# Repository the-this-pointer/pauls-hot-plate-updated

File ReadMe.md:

#### Paul's Hotplate Upgraded

This is another version of awesome pauls hot plate project that I am working on. I designed a pcb for the project because I don't have access to the board he used in his project.
The project is not completed yet and I should do some modifications on the enclosure, and I need to change the firmware to support the new PCB. Also the enclosure and the PCB is not tested.

External component libraries located [here](https://github.com/the-this-pointer/kicad-my-libraries)

###### TODO:

- Firmware for new PCB
- Enclosure for new PCB

#### Images

The enclosure files and images are for revision `54e05cd389d`, the boards are changed afterwards and I will redesign enclosure.

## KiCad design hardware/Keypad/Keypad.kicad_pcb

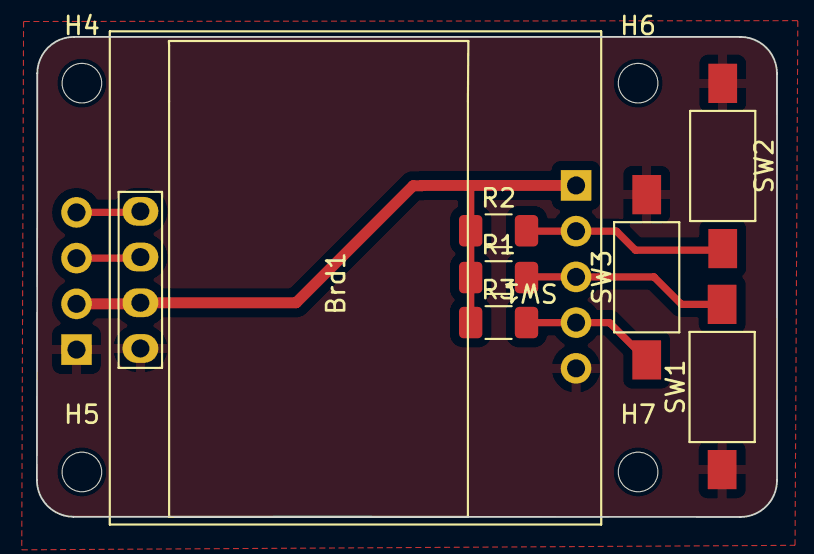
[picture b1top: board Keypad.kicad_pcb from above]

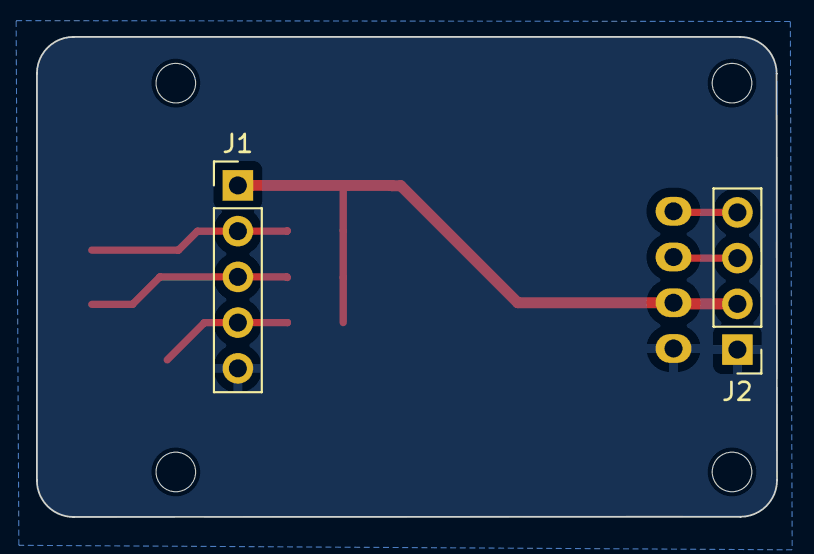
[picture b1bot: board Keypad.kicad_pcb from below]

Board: 2 copper layers, 41.1 x 26.7 mm, 13 parts (2 on the bottom side), 7 nets.

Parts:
Brd1: SSD1306; 128x64OLED
H4, H5, H6, H7: MountingHole; MountingHole_2.2mm_M2
J1: Keypad1; PinHeader_1x05_P2.54mm_Vertical
J2: LCD; PinHeader_1x04_P2.54mm_Vertical
R1, R2, R3: 10k; R_1206_3216Metric_Pad1.30x1.75mm_HandSolder
SW1: LEFT; SW_SPST_FSMSM
SW2: RIGHT; SW_SPST_FSMSM
SW3: SET; SW_SPST_FSMSM

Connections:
+3V3: Brd1.2 (VCC), J1.1, J2.2, R1.1, R2.1, R3.1
/IO12: J1.4, R3.2, SW3.2 (B)
/IO13: J1.2, R2.2, SW2.2 (B)
/IO14: J1.3, R1.2, SW1.2 (B)
/SCK: Brd1.3 (SCL), J2.3
/SDA: Brd1.4 (SDA), J2.4
GND: Brd1.1 (GND), J1.5, J2.1, SW1.1 (A), SW2.1 (A), SW3.1 (A)

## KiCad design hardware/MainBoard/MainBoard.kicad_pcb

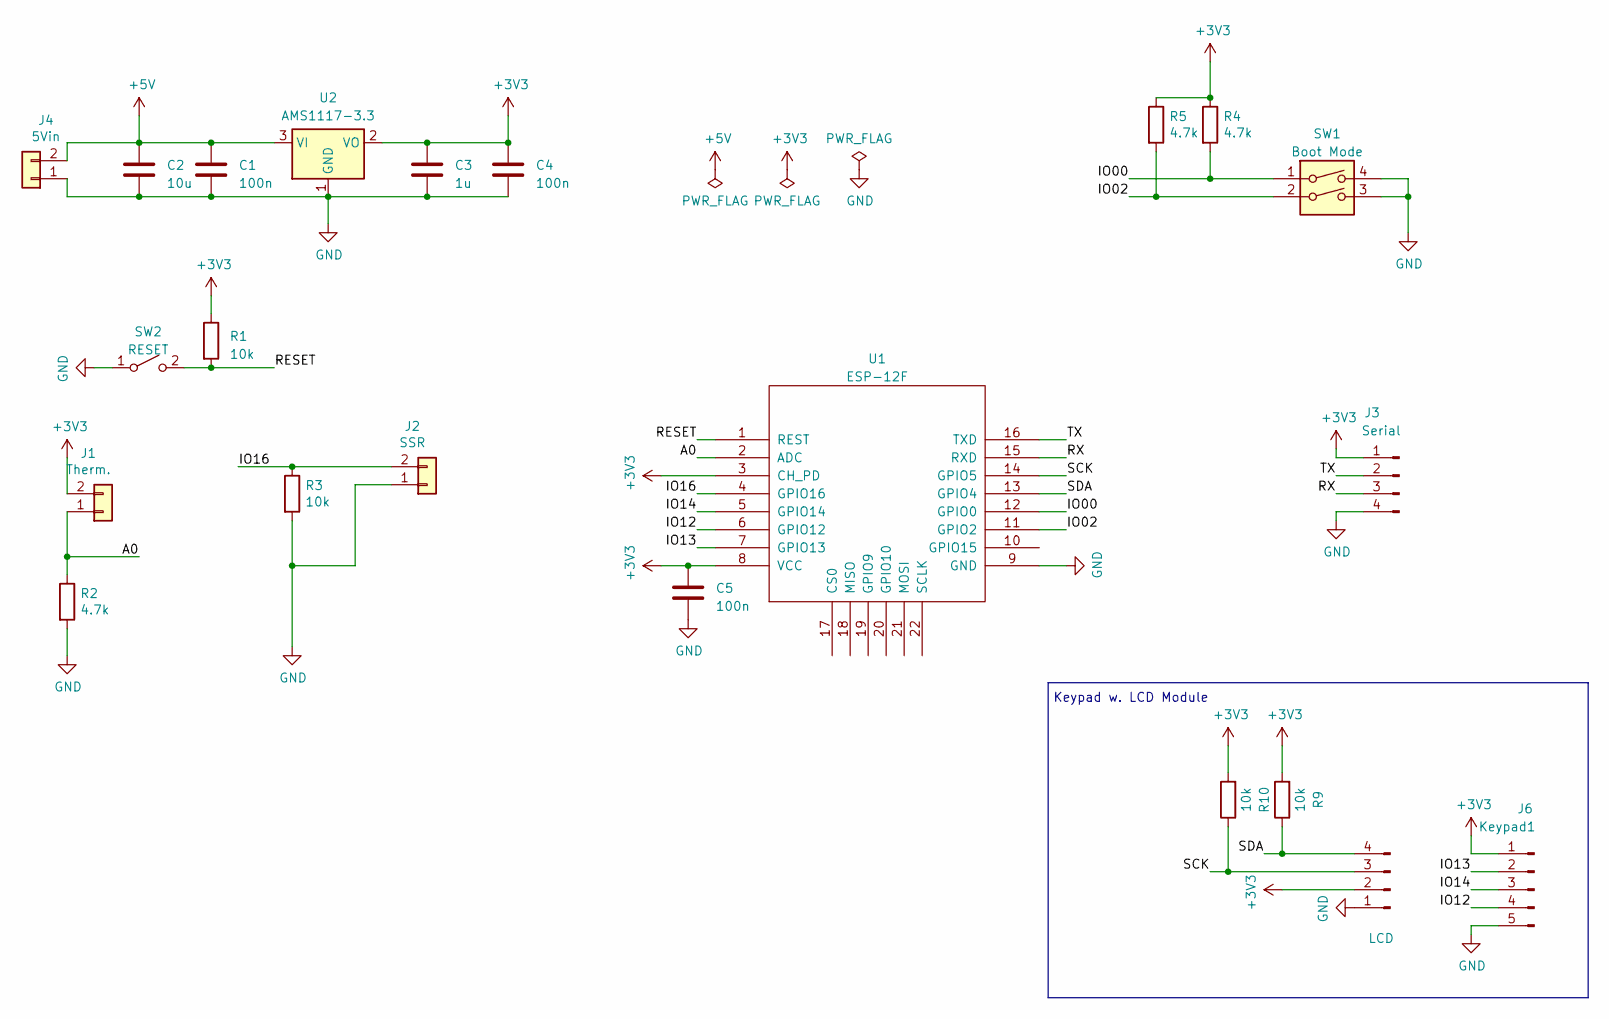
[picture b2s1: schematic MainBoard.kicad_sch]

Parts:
C1, C4, C5: 100n; C_1206_3216Metric_Pad1.33x1.80mm_HandSolder
C2: 10u; C_1206_3216Metric_Pad1.33x1.80mm_HandSolder
C3: 1u; C_1206_3216Metric_Pad1.33x1.80mm_HandSolder
J1: Therm.; JST_XH_B2B-XH-A_1x02_P2.50mm_Vertical
J2: SSR; JST_XH_B2B-XH-A_1x02_P2.50mm_Vertical
J3: Serial; PinHeader_1x04_P2.54mm_Vertical
J4: 5Vin; JST_XH_B2B-XH-A_1x02_P2.50mm_Vertical
J5: LCD; PinHeader_1x04_P2.54mm_Vertical
J6: Keypad1; PinHeader_1x05_P2.54mm_Vertical
R1, R3, R9, R10: 10k; R_1206_3216Metric_Pad1.30x1.75mm_HandSolder
R2, R4, R5: 4.7k; R_1206_3216Metric_Pad1.30x1.75mm_HandSolder
SW1: Boot Mode; SW_DIP_SPSTx02_Slide_9.78x7.26mm_W7.62mm_P2.54mm
SW2: RESET; SW_SPST_FSMSM
U1: ESP-12F; ESP-07-RF_Modules
U2: AMS1117-3.3; SOT-223-3_TabPin2

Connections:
+3V3: C3.1, C4.1, C5.1, J1.2, J3.1, J5.2, J6.1, R1.1, R4.1, R5.1, R9.2, R10.2, U1.3 (CH_PD), U1.8 (VCC), U2.2 (VO)
+5V: C1.1, C2.1, J4.2, U2.3 (VI)
/A0: J1.1, R2.1, U1.2 (ADC)
/IO00: R4.2, SW1.1, U1.12 (GPIO0)
/IO02: R5.2, SW1.2, U1.11 (GPIO2)
/IO12: J6.4, U1.6 (GPIO12)
/IO13: J6.2, U1.7 (GPIO13)
/IO14: J6.3, U1.5 (GPIO14)
/IO16: J2.2, R3.1, U1.4 (GPIO16)
/RESET: R1.2, SW2.2 (B), U1.1 (REST)
/RX: J3.3, U1.15 (RXD)
/SCK: J5.3, R10.1, U1.14 (GPIO5)
/SDA: J5.4, R9.1, U1.13 (GPIO4)
/TX: J3.2, U1.16 (TXD)
GND: C1.2, C2.2, C3.2, C4.2, C5.2, J2.1, J3.4, J4.1, J5.1, J6.5, R2.2, R3.2, SW1.3, SW1.4, SW2.1 (A), U1.9 (GND), U2.1 (GND)

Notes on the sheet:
Keypad w. LCD Module

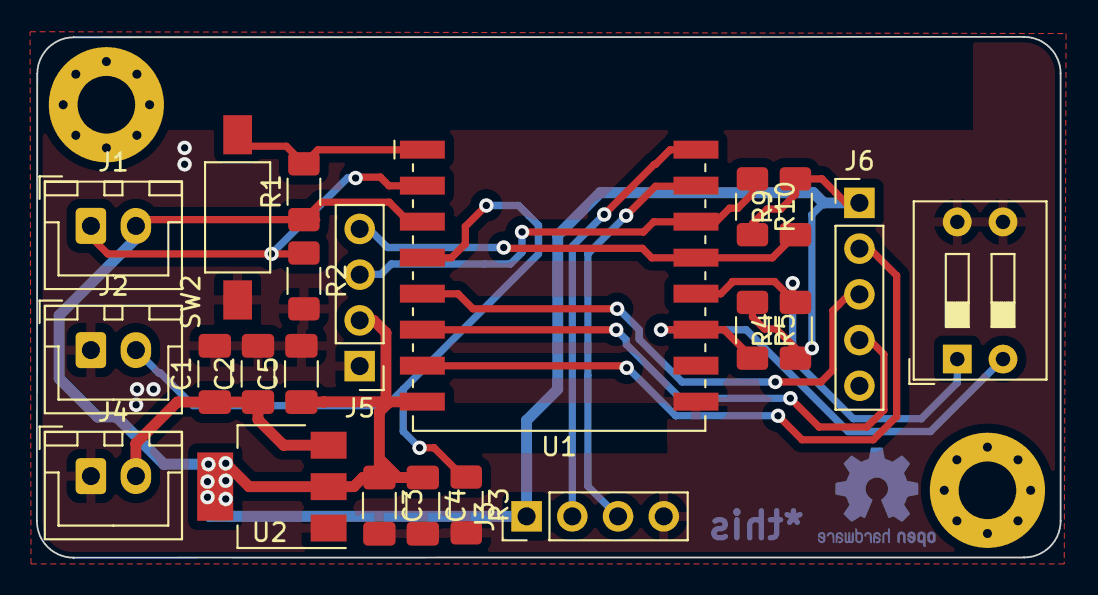
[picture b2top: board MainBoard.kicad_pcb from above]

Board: 2 copper layers, 56.9 x 28.9 mm, 22 parts (0 on the bottom side), 15 nets.

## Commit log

2023-07-09 pcb added
2023-07-09 enclosure added
2023-07-09 images added
2023-07-13 readme file added
2023-07-13 keypad added
2023-07-31 gme12864 replaced with ssd1306
2023-07-31 libraries updated
2023-07-31 readme updated
2023-08-02 3d model for keypad connector updated
2023-08-02 new design of enclosure based on new lcd and snap fit joints
2023-08-02 readme file updated
2023-08-02 fix keypad connector location on board
2023-08-02 fix bolt holes on box body
2024-06-14 redesign pcb files
2024-06-21 minor change on keypad
